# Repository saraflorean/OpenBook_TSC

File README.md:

# OpenBook_TSC

## Florean Sara-Denisa - 333CD

# Diagrama Block

---

# Descrierea modulelor hardware

## Microcontroler – ESP32-C6-WROOM-1-N8

ESP32-C6 este unitatea centrală de procesare responsabilă pentru gestionarea tuturor operațiunilor sistemului, comunicarea cu senzorii și modulele, precum și managementul energiei.

- **Arhitectură:** RISC-V pe 32 de biți  
- **Frecvență ceas:** 160 MHz  
- **Conectivitate wireless:** Wi-Fi 6 la 2.4 GHz, Bluetooth 5.0  

## Management Energetic & Baterie

- **Tip baterie:** Li-Po (Litiu-Polimer)  
- **Capacitate:** 3.7V, 1800mAh  
- **Circuit de încărcare:** MCP73831T  
- **Tensiune de intrare:** 5V prin USB-C  
- **Protecții:** Protecție la supraîncărcare și descărcare profundă  
- **Regulator de tensiune:** Regulator LDO care asigură o alimentare stabilă de 3.3V pentru toate componentele
  
## Afișaj – Ecran E-Paper (E-Ink)

- **Dimensiune:** 7.5 inci  
- **Rezoluție:** 800x480 pixeli  
- **Interfață de comunicare:** SPI  

## Modul Card SD

- **Tip:** MicroSD (Suportă FAT32)  
- **Interfață:** SPI  

## Memorie NOR Flash Externă

- **Capacitate:** 64MB  
- **Interfață:** SPI  

## Senzor de Mediu – BME688

- **Funcții:** Măsoară temperatura, umiditatea, presiunea aerului și nivelurile de gaz  
- **Interfață de comunicare:** I2C  

## Ceas în Timp Real (RTC) – DS3231SN

- **Funcționalitate:** Păstrează ora și data chiar și atunci când sistemul este oprit  
- **Interfață de comunicare:** I2C  

## Conector USB-C & Protecție ESD

- **Funcționalitate:** Asigură alimentarea și transferul de date  
- **Protecție:** Protecție ESD integrată și diodă Schottky pentru protecție la polaritate inversă  

## Butoane & Interacțiune cu Utilizatorul

- **Butoane tactile (push):** Utilizate pentru control manual  

## Interfețe de Comunicație

- **GPIO:** Folosit pentru controlul butoanelor și operațiuni generale I/O  
- **SPI:** Utilizat pentru cardul SD, memoria flash externă și ecranul e-paper  
- **I2C:** Utilizat pentru senzorul de mediu BME688 și modulul RTC DS3231SN  
- **UART:** Utilizat pentru depanare și comunicație serială  
- **Wi-Fi & Bluetooth:** Asigurate de ESP32-C6 pentru conectivitate wireless  

---

## Lista Componentelor folosite

| Componentă | Link | Fișă Tehnică |
|-----------|--------------|-----------|
| MAX17048G+T10 | [Model](https://www.snapeda.com/parts/MAX17048G+T10/Analog+Devices/view-part/?ref=eda) | [Datasheet](https://www.alldatasheet.com/view.jsp?Searchword=Max17048&gad_source=1&gbraid=0AAAAADcdDU8aYfZtfJfdZ9I5j6RwZ_cbA&gclid=Cj0KCQjwqcO_BhDaARIsACz62vNa9xrVfzjCjADRwXD0RBbo4Nret3ywwteDGLJKZui8ZL8KdVlTE7caAvQxEALw_wcB) |
| MCP73831T-5ACI/OT | [Model](https://www.mouser.co.uk/ProductDetail/Microchip-Technology/MCP73831T-5ACI-OT?qs=hH%252BOa0VZEiAcgAcEkuamXg%3D%3D) | [Datasheet](//efaidnbmnnnibpcajpcglclefindmkaj/https://ww1.microchip.com/downloads/en/DeviceDoc/MCP73831-Family-Data-Sheet-DS20001984H.pdf) |
| USB4110-GF-A  | [Model](https://componentsearchengine.com/part-view/USB4110-GF-A/GCT%20(GLOBAL%20CONNECTOR%20TECHNOLOGY)) | [Datasheet](//efaidnbmnnnibpcajpcglclefindmkaj/https://gct.co/files/drawings/usb4110.pdf) |
| Adafruit | [Model](https://eu.mouser.com/ProductDetail/Adafruit/4208?qs=PzGy0jfpSMtbScLbr0L5dw%3D%3D) | [Datasheet](https://www.arrow.com/en/manufacturers/adafruit-industries/datasheets) |
| CAPACITOR | [Model](https://componentsearchengine.com/part-view/R0402%201%25%20100%20K%20(RC0402FR-07100KL)/YAGEO) | [Datasheet](//efaidnbmnnnibpcajpcglclefindmkaj/https://www.resistor.com/assets/pdf/0402tstd.pdf) |
| CPH3225A | [Model](https://www.snapeda.com/parts/CPH3225A/Seiko+Instruments/view-part/?ref=eda) | [Datasheet](https://octopart.com/datasheet/cph3225a-seiko-25340571) |
| EVQPUJ02K | [Model](https://industry.panasonic.com/global/en/products/control/switch/light-touch/number/evqpuj02k) | [Datasheet](https://www.lcsc.com/datasheet/lcsc_datasheet_2201121800_PANASONIC-EVQPUJ02K_C2936858.pdf) |
| KP-1608SURCK | [Model](https://www.snapeda.com/parts/KP-1608SURCK/Kingbright/view-part/?ref=search&t=LED%200603) | [Datasheet](//efaidnbmnnnibpcajpcglclefindmkaj/https://media.elv.com/file/107153_led_surck1608_data.pdf) |
| USBLC6-2SC6Y | [Model](https://www.snapeda.com/parts/USBLC6-2SC6Y/STMicroelectronics/view-part/?ref=eda) | [Datasheet](https://www.digikey.com/en/htmldatasheets/production/1375342/0/0/1/usblc6-2sc6y) |
| SD0805S020S1R0 | [Model](https://ro.mouser.com/ProductDetail/KYOCERA-AVX/SD0805S020S1R0?qs=jCA%252BPfw4LHbpkAoSnwrdjw%3D%3D) | [Datasheet](https://www.alldatasheet.com/view.jsp?Searchword=SD0805S&sField=2) |
| PGB1010603MR | [Model](https://www.snapeda.com/parts/PGB1010603MR/Littelfuse/view-part/?ref=eda) | [Datasheet](https://www.alldatasheet.com/view.jsp?Searchword=Pgb1010603mr&gad_source=1&gbraid=0AAAAADcdDU8aYfZtfJfdZ9I5j6RwZ_cbA&gclid=Cj0KCQjwqcO_BhDaARIsACz62vOPBOBe0eOh5gDUFkkKl4JBcbmoFZYtJ8BOnbaWqr_BuUCcVWvbutAaAmGkEALw_wcB) |
| BD5229G-TR  | [Model](https://componentsearchengine.com/part-view/BD5229G-TR/ROHM%20Semiconductor) | [Datasheet](https://www.lcsc.com/datasheet/lcsc_datasheet_2201131330_ROHM-Semicon-BD5229G-TR_C962636.pdf) |
| BME680 | [Model](https://www.snapeda.com/parts/BME680/Bosch/view-part/?welcome=home) | [Datasheet](//efaidnbmnnnibpcajpcglclefindmkaj/https://www.bosch-sensortec.com/media/boschsensortec/downloads/datasheets/bst-bme680-ds001.pdf) |
| XC6220A331MR-G | [Model](https://componentsearchengine.com/part-view/XC6220A331MR-G/Torex) | [Datasheet](https://www.alldatasheet.com/view.jsp?Searchword=Xc6220&gad_source=1&gbraid=0AAAAADcdDU8aYfZtfJfdZ9I5j6RwZ_cbA&gclid=Cj0KCQjwqcO_BhDaARIsACz62vPS06NB6tLgniZzfaVpKNu1m811BNk6AEPfg4DbP6f5S8QWA_pW_UQaAv-0EALw_wcB) |
| SMD Solder | [Model](https://grabcad.com/library/solder-jumpers-1) | [Datasheet]() |
| BUTTON | [Model](https://industry.panasonic.com/global/en/products/control/switch/light-touch/number/evqpuj02k) | [Datasheet](https://www.lcsc.com/datasheet/lcsc_datasheet_2201121800_PANASONIC-EVQPUJ02K_C2936858.pdf) |
| Bobina | [Model](https://store.comet.srl.ro/Catalogue/Product/43497/) | [Datasheet](https://www.scribd.com/document/814581278/Datasheet-Bobina) |
| PFMF | [Model](https://www.mouser.co.uk/ProductDetail/EPCOS-TDK/B72520T0350K062?qs=dEfas%2FXlABIszF52uu7vrg%3D%3D) | [Datasheet](https://ro.mouser.com/c/ds/circuit-protection/thermistors/resettable-fuses-pptc/?m=Schurter&series=PFMF) |
| DMG2305UX-7 | [Model](https://componentsearchengine.com/part-view/DMG2305UX-7/Diodes%20Incorporated) | [Datasheet](//efaidnbmnnnibpcajpcglclefindmkaj/https://www.mouser.com/datasheet/2/115/DMG2305UX-266242.pdf?srsltid=AfmBOop22k34YTJJra1xubiU6LPiN4M4JlcWbRoSNdxSGFak8uWgXPpK) |
| Si1308EDL-T1-GE3 | [Model](https://componentsearchengine.com/part-view/SI1308EDL-T1-GE3/Vishay) | [Datasheet](https://www.alldatasheet.com/view.jsp?Searchword=Si1308edl&gad_source=1&gbraid=0AAAAADcdDU-px713ONYSnQ2O-gcwqYcFq&gclid=Cj0KCQjwqcO_BhDaARIsACz62vN_Nz3MJOc6J_03gnVBm7aSqC8v9wyP0VD-iRKP-gFrYgdhLi99I14aAlVJEALw_wcB) |
| R0402 | [Model](https://componentsearchengine.com/part-view/R0402%201%25%20100%20K%20(RC0402FR-07100KL)/YAGEO) | [Datasheet](//efaidnbmnnnibpcajpcglclefindmkaj/https://www.resistor.com/assets/pdf/0402tstd.pdf) |
| W25Q512JVEIQ | [Model](https://www.snapeda.com/parts/ESP32-C6-WROOM-1-N8/Espressif+Systems/view-part/?ref=eda) | [Datasheet](//efaidnbmnnnibpcajpcglclefindmkaj/https://www.mouser.com/datasheet/2/949/W25Q512JV_SPI_RevB_06252019_KMS-2487502.pdf?srsltid=AfmBOoquExqDVgxEELF9CzuOGxHos0CD1nQDROHD6Eebdm2foNzqozqU) |
| ESP32-C6-WROOM-1-N8 | [Model](https://www.snapeda.com/parts/ESP32-C6-WROOM-1-N8/Espressif+Systems/view-part/?ref=eda) | [Datasheet](//efaidnbmnnnibpcajpcglclefindmkaj/https://www.mouser.com/catalog/specsheets/Espressif_ESP32_C6_WROOM_1%20_Datasheet_V0.1_PRELIMINARY_en.pdf?srsltid=AfmBOooHQKNitqODRaaPjoZInfWKTacDER1t5uRK6sKqT13TrzvVo_B7) |
| DS3231SN# | [Model](https://www.snapeda.com/parts/DS3231SN%23/Analog+Devices/view-part/?ref=eda) | [Datasheet](https://www.alldatasheet.com/view.jsp?Searchword=Ds3231sn%20datasheet&gad_source=1&gbraid=0AAAAADcdDU-Gy9URfMxGmqiPg7ci5L3wR&gclid=Cj0KCQjwqcO_BhDaARIsACz62vMkK3ETSnW2w7mo0Fa-wgWJGn89AxWCyIND6k5X8MmoPl6hv6VWwT8aAiS-EALw_wcB) |

---

## Mapare Pini – ESP32-C6

| Denumire       | Pin GPIO      | Utilizare                                |
|----------------|---------------|------------------------------------------|
| Buton Reset    | EN            | Resetare ESP32-C6                        |
| INT_RTC        | IO0           | Semnal de întrerupere de la RTC (DS3231)|
| 32KHZ          | IO1           | Semnal de ceas 32 kHz                    |
| MISO (SPI)     | IO2           | Recepție date SPI                        |
| EPD BUSY       | IO3           | Indicator stare E-Paper                  |
| SS_SD          | IO4           | Chip Select pentru card SD (SPI)        |
| EPD DC         | IO5           | Data/Command pentru E-Paper             |
| SCK (SPI)      | IO6           | Clock pentru SPI                         |
| MOSI (SPI)     | IO7           | Transmitere date SPI                     |
| Buton Boot     | IO9           | Intrare în bootloader                    |
| 3V3            | 3V3           | Alimentare 3.3V                          |
| EPD_CS         | IO10          | Selectare SPI pentru E-Paper            |
| FLASH_CS       | IO11          | Selectare SPI pentru NOR Flash          |
| USB_D-         | IO12          | Linie diferențială USB (minus)          |
| USB_D+         | IO13          | Linie diferențială USB (plus)           |
| Buton Change   | IO15          | Schimbare mod operare                    |
| TX (UART)      | TXD0/GPIO16   | Transmitere date UART                   |
| RX (UART)      | RXD0/GPIO17   | Recepție date UART                      |
| RTC_RST        | IO18          | Reset extern/semnal RTC                 |
| I2C_PW         | IO19          | Linie de alimentare / enable pentru I2C |
| EPD_3V3_C      | IO20          | Linie de alimentare 3.3V pentru E-Paper |
| SDA (I2C)      | IO21          | Linie de date I2C                       |
| SCL (I2C)      | IO22          | Linie de ceas I2C                       |
| EPD RST        | IO23          | Resetare E-Paper                        |

---

## Informații adiționale

**Erori SMD-Hole Board Outline Clearance la Mufa USB:**  
  - Am identificat două erori de tip **SMD-Hole Board Outline Clearance** asociate mufei USB. Conform informațiilor tehnice primite, aceste erori au fost **acceptate**.

**Redimensionarea și amplasarea componentelor:**
  - Dimensiunile unor componente au fost **ajustate** pentru a rezolva incompatibilitățile detectate de verificatorul de design.
  - Condensatori de decuplare de 100nF au fost **amplasați aproape de pinii de alimentare** ai circuitelor integrate (IC), în conformitate cu practicile standard de proiectare pentru reducerea zgomotului electric.
  - Componentele au fost amplasate respectând pe cât de mult posibil **specifcațiile proiectului** asigurând compatibilitatea dintre carcasa oferită și dimensiunile PCB-ului.
  - **TP-urile** au fost amplasate diferit față de specificațiile oferite, pentru a facilita o rutare eficientă. Poziția lor fiind determinată de apropierea de piesele conectate.

 **Rutare și planuri de masă**
 - **Traseele de alimentare** au fost rutate **doar pe stratul superior**, ceea ce a necesitat utilizarea a aproximativ 100 de vias-uri pentru a permite rutarea semnalelor pe stratul inferior.
 - **Planul de masă** (GND) a fost adăugat după finalizarea rutării, aplicat atât pe stratul superior, cât și pe cel inferior, pentru a asigura o împământare cu impedanță redusă și pentru a diminua interferențele electromagnetice (EMI).
 - Am realizat **via stitching** în regiunile unde planurile de masă de pe stratul superior și inferior se suprapuneau, pentru a asigura o conexiune electrică solidă între acestea.

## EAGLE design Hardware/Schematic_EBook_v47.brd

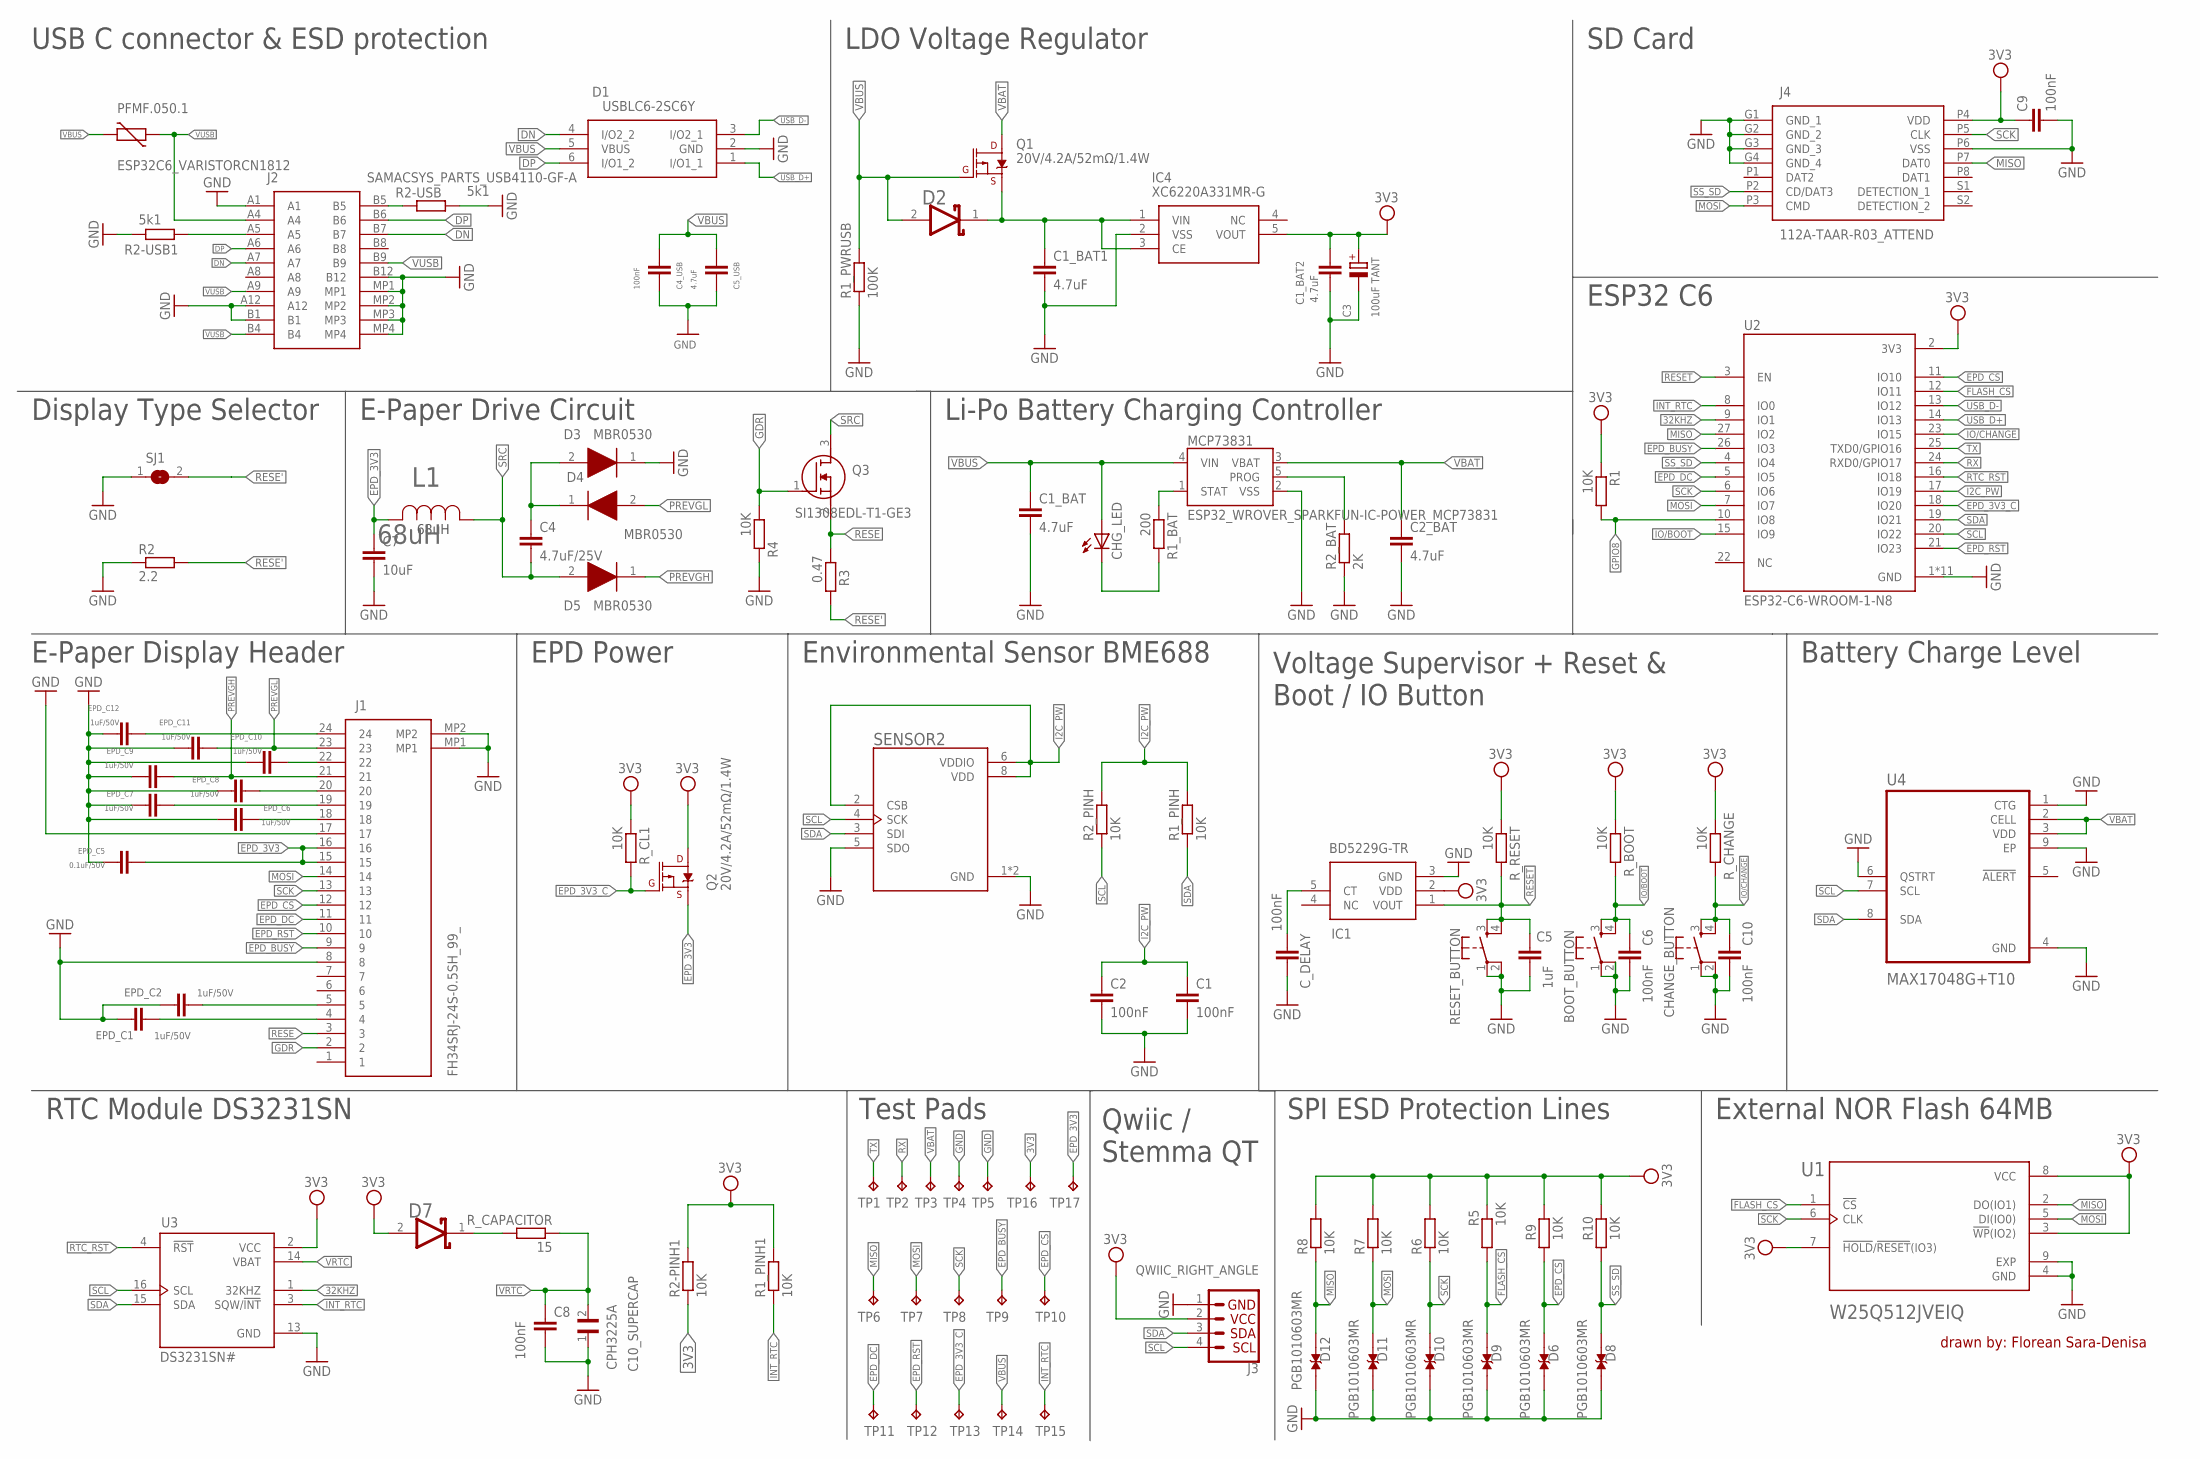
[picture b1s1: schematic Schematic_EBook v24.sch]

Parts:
BOOT_BUTTON: BUTTON_CUSYOMV1; MYBUTTON
C1, C2, C4_USB, C6, C8, C9, C10: 100nF; EAGLE-LTSPICE_C0402
C1_BAT, C1_BAT1, C1_BAT2, C2_BAT, C5_USB: 4.7uF; EAGLE-LTSPICE_C0402
C3: 100uF TANT; RCL_CT3528
C4: 4.7uF/25V; EAGLE-LTSPICE_C0402
C5: 1uF; EAGLE-LTSPICE_C0402
C7: 10uF; EAGLE-LTSPICE_C0402
C10_SUPERCAP: CPH3225A; CAPCP3225X100N
CHANGE_BUTTON: BUTTON_CUSYOMV1; MYBUTTON
CHG_LED: &; ADAFRUIT_CHIP-LED0603
C_DELAY: 100nF; EAGLE-LTSPICE_C0402
D1: USBLC6-2SC6Y; SOT95P280X145-6N
D2, D7: ESP32_WROVER_AVX---SD0805S020S1R0_AVX_SD0805S020S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; ESP32_WROVER_AVX---SD0805S020S1R0_AVX_SD0805S020S1R0_0
D3, D4, D5: MBR0530; SOD3716X135N
D6, D8, D9, D10, D11, D12: PGB1010603MR; DIOC1608X36N
EPD_C1, EPD_C2, EPD_C6, EPD_C7, EPD_C8, EPD_C9, EPD_C10, EPD_C11, EPD_C12: 1uF/50V; EAGLE-LTSPICE_C0402
EPD_C5: 0.1uF/50V; EAGLE-LTSPICE_C0402
IC1: BD5229G-TR; SOT95P280X125-5N
IC4: XC6220A331MR-G; SOT95P280X120-5N
J1: FH34SRJ-24S-0.5SH_99_; FH34SRJ24S05SH99
J2: SAMACSYS_PARTS_USB4110-GF-A; SAMACSYS_PARTS_USB4110GFA
J3: QWIIC_RIGHT_ANGLE; JST04_1MM_RA
J4: 112A-TAAR-R03_ATTEND; 112ATAARR03ATTEND
L1: 68uH; IND_4828-WE-TPC_WRE
MCP73831: ESP32_WROVER_SPARKFUN-IC-POWER_MCP73831; ESP32_WROVER_SPARKFUN-IC-POWER_SOT23-5
PFMF.050.1: ESP32C6_VARISTORCN1812; ESP32C6_VARISTOR_CT/CN1812
Q1, Q2: 20V/4.2A/52mΩ/1.4W; ESP32_WROVER_SPARKFUN-DISCRETESEMI_SOT23-3
Q3: SI1308EDL-T1-GE3; SOT65P210X110-3N
R1, R1_PINH, R1_PINH1, R2-PINH1, R2_PINH, R4, R5, R6, R7, R8, R9, R10: 10K; ESP32_WROVER_EAGLE-LTSPICE_R0402
R1_BAT: 200; ESP32_WROVER_EAGLE-LTSPICE_R0402
R1_PWRUSB: 100K; ESP32_WROVER_EAGLE-LTSPICE_R0402
R2: 2.2; ESP32_WROVER_EAGLE-LTSPICE_R0402
R2-USB, R2-USB1: 5k1; ESP32_WROVER_EAGLE-LTSPICE_R0402
R2_BAT: 2K; ESP32_WROVER_EAGLE-LTSPICE_R0402
R3: 0.47; ESP32_WROVER_EAGLE-LTSPICE_R0402
RESET_BUTTON: BUTTON_CUSYOMV1; MYBUTTON
R_BOOT: 10K; ESP32_WROVER_EAGLE-LTSPICE_R0402
R_CAPACITOR: 15; ESP32_WROVER_EAGLE-LTSPICE_R0402
R_CHANGE: 10K; ESP32_WROVER_EAGLE-LTSPICE_R0402
R_CL1: 10K; ESP32_WROVER_EAGLE-LTSPICE_R0402
R_RESET: 10K; ESP32_WROVER_EAGLE-LTSPICE_R0402
SENSOR2: ESP32_WROVER_BME680_BME680; ESP32_WROVER_BME680_PSON80P300X300X100-8N
SJ1: &; SJ
TP1, TP2, TP3, TP4, TP5, TP6, TP7, TP8, TP9, TP10, TP11, TP12, TP13, TP14, TP15, TP16, TP17: TPTP20R; TP20R
U1: W25Q512JVEIQ; SON127P600X800X80-9N
U2: ESP32-C6-WROOM-1-N8; XCVR_ESP32-C6-WROOM-1-N8
U3: DS3231SN#; SOIC127P1032X265-16N
U4: MAX17048G+T10; SON50P200X200X80-9N

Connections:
3V3: C1_BAT2.1, C3.+, C9.1, D7.2 (ANODE), IC1.2 (VDD), IC4.5 (VOUT), J3.2, J4.P4 (VDD), Q2.3 (D), R1.1, R1_PINH1.2, R2-PINH1.1, R2-PINH1.2, R5.2, R6.2, R7.2, R8.2, R9.2, R10.2, R_BOOT.1, R_CHANGE.1, R_CL1.1, R_RESET.1, TP16.TP, U1.3 (!WP!(IO2)), U1.7 (!HOLD!/!RESET!(IO3)), U1.8 (VCC), U2.2 (3V3), U3.2 (VCC)
32KHZ: U2.9 (IO1), U3.1 (32KHZ)
DN: D1.4 (I/O2_2), J2.A7, J2.B7
DP: D1.6 (I/O1_2), J2.A6, J2.B6
EPD_3V3: C7.1, EPD_C5.1, J1.15, J1.16, L1.2, Q2.2 (S), TP17.TP
EPD_3V3_C: Q2.1 (G), R_CL1.2, TP13.TP, U2.18 (IO20)
EPD_BUSY: J1.9, TP9.TP, U2.26 (IO3)
EPD_CS: D6.2, J1.12, R9.1, TP10.TP, U2.11 (IO10)
EPD_DC: J1.11, TP11.TP, U2.5 (IO5)
EPD_RST: J1.10, TP12.TP, U2.21 (IO23)
FLASH_CS: D9.2, R5.1, U1.1 (!CS), U2.12 (IO11)
GDR: J1.2, Q3.1 (G), R4.1
GND: BOOT_BUTTON.1, BOOT_BUTTON.2, C1.2, C1_BAT.2, C1_BAT1.2, C1_BAT2.2, C2.2, C2_BAT.2, C3.-, C4_USB.2, C5.2, C5_USB.2, C6.2, C7.2, C8.2, C9.2, C10.2, C10_SUPERCAP.1, CHANGE_BUTTON.1, CHANGE_BUTTON.2, C_DELAY.2, D1.2 (GND), D3.1 (K), D6.1, D8.1, D9.1, D10.1, D11.1, D12.1, EPD_C1.2, EPD_C2.2, EPD_C5.2, EPD_C6.2, EPD_C7.2, EPD_C8.2, EPD_C9.2, EPD_C10.2, EPD_C11.2, EPD_C12.2, IC1.3 (GND), IC4.2 (VSS), J1.8, J1.17, J1.MP1, J1.MP2, J2.A1, J2.A12, J2.B1, J2.B12, J2.MP1, J2.MP2, J2.MP3, J2.MP4, J3.1, J4.G1 (GND_1), J4.G2 (GND_2), J4.G3 (GND_3), J4.G4 (GND_4), J4.P6 (VSS), MCP73831.2 (VSS), R1_PWRUSB.1, R2.1, R2-USB.2, R2-USB1.1, R2_BAT.1, R4.2, RESET_BUTTON.1, RESET_BUTTON.2, SENSOR2.1 (GND), SENSOR2.5 (SDO), SENSOR2.7 (GND), SJ1.1, TP4.TP, TP5.TP, U1.4 (GND), U1.9 (EXP), U2.1 (GND), U2.28 (GND), U2.29_1 (GND), U2.29_2 (GND), U2.29_3 (GND), U2.29_4 (GND), U2.29_5 (GND), U2.29_6 (GND), U2.29_7 (GND), U2.29_8 (GND), U2.29_9 (GND), U3.13 (GND), U4.1 (CTG), U4.4 (GND), U4.6 (QSTRT), U4.9 (EP)
GPIO8: R1.2, U2.10 (IO8)
I2C_PW: C1.1, C2.1, R1_PINH.2, R2_PINH.2, SENSOR2.2 (CSB), SENSOR2.6 (VDDIO), SENSOR2.8 (VDD), U2.17 (IO19)
INT_RTC: R1_PINH1.1, TP15.TP, U2.8 (IO0), U3.3 (SQW/!INT)
IO/BOOT: BOOT_BUTTON.3, BOOT_BUTTON.4, C6.1, R_BOOT.2, U2.15 (IO9)
IO/CHANGE: C10.1, CHANGE_BUTTON.3, CHANGE_BUTTON.4, R_CHANGE.2, U2.23 (IO15)
MISO: D12.2, J4.P7 (DAT0), R8.1, TP6.TP, U1.2 (DO(IO1)), U2.27 (IO2)
MOSI: D11.2, J1.14, J4.P3 (CMD), R7.1, TP7.TP, U1.5 (DI(IO0)), U2.7 (IO7)
unnamed: J2.A5, R2-USB1.2
unnamed: J2.B5, R2-USB.1
unnamed: C1_BAT1.1, D2.1 (CATHODE), IC4.1 (VIN), IC4.3 (CE), Q1.2 (S)
unnamed: MCP73831.1 (STAT), R1_BAT.1
unnamed: C4.1, D3.2 (A), D4.1 (K)
unnamed: CHG_LED.C, R1_BAT.2
unnamed: MCP73831.5 (PROG), R2_BAT.2
unnamed: EPD_C2.1, J1.5
unnamed: EPD_C1.1, J1.4
unnamed: C_DELAY.1, IC1.5 (CT)
unnamed: D7.1 (CATHODE), R_CAPACITOR.2
unnamed: EPD_C12.1, J1.24
unnamed: EPD_C10.1, J1.22
unnamed: EPD_C8.1, J1.20
unnamed: EPD_C6.1, J1.18
unnamed: EPD_C7.1, J1.19
PREVGH: D5.1 (K), EPD_C9.1, J1.21
PREVGL: D4.2 (A), EPD_C11.1, J1.23
RESE: J1.3, Q3.2 (S), R3.1
RESE': R2.2, R3.2, SJ1.2
RESET: C5.1, IC1.1 (VOUT), RESET_BUTTON.3, RESET_BUTTON.4, R_RESET.2, U2.3 (EN)
RTC_RST: U2.16 (IO18), U3.4 (!RST)
RX: TP2.TP, U2.24 (RXD0/GPIO17)
SCK: D10.2, J1.13, J4.P5 (CLK), R6.1, TP8.TP, U1.6 (CLK), U2.6 (IO6)
SCL: J3.4, R2_PINH.1, SENSOR2.4 (SCK), U2.20 (IO22), U3.16 (SCL), U4.7 (SCL)
SDA: J3.3, R1_PINH.1, SENSOR2.3 (SDI), U2.19 (IO21), U3.15 (SDA), U4.8 (SDA)
SRC: C4.2, D5.2 (A), L1.1, Q3.3 (D)
SS_SD: D8.2, J4.P2 (CD/DAT3), R10.1, U2.4 (IO4)
TX: TP1.TP, U2.25 (TXD0/GPIO16)
USB_D+: D1.1 (I/O1_1), U2.14 (IO13)
USB_D-: D1.3 (I/O2_1), U2.13 (IO12)
VBAT: C2_BAT.1, MCP73831.3 (VBAT), Q1.3 (D), TP3.TP, U4.2 (CELL), U4.3 (VDD)
VBUS: C1_BAT.1, C4_USB.1, C5_USB.1, CHG_LED.A, D1.5 (VBUS), D2.2 (ANODE), MCP73831.4 (VIN), PFMF.050.1.2, Q1.1 (G), R1_PWRUSB.2, TP14.TP
VRTC: C8.1, C10_SUPERCAP.2, R_CAPACITOR.1, U3.14 (VBAT)
VUSB: J2.A4, J2.A9, J2.B4, J2.B9, PFMF.050.1.1

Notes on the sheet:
68uH
USB C connector & ESD protection
LDO Voltage Regulator
SD Card
ESP32 C6
Li-Po Battery Charging Controller
E-Paper Drive Circuit
Display Type Selector
E-Paper Display Header
EPD Power
Environmental Sensor BME688
Voltage Supervisor + Reset & Boot / IO Button
Battery Charge Level
External NOR Flash 64MB
SPI ESD Protection Lines
Qwiic / Stemma QT
Test Pads
RTC Module DS3231SN
drawn by: Florean Sara-Denisa

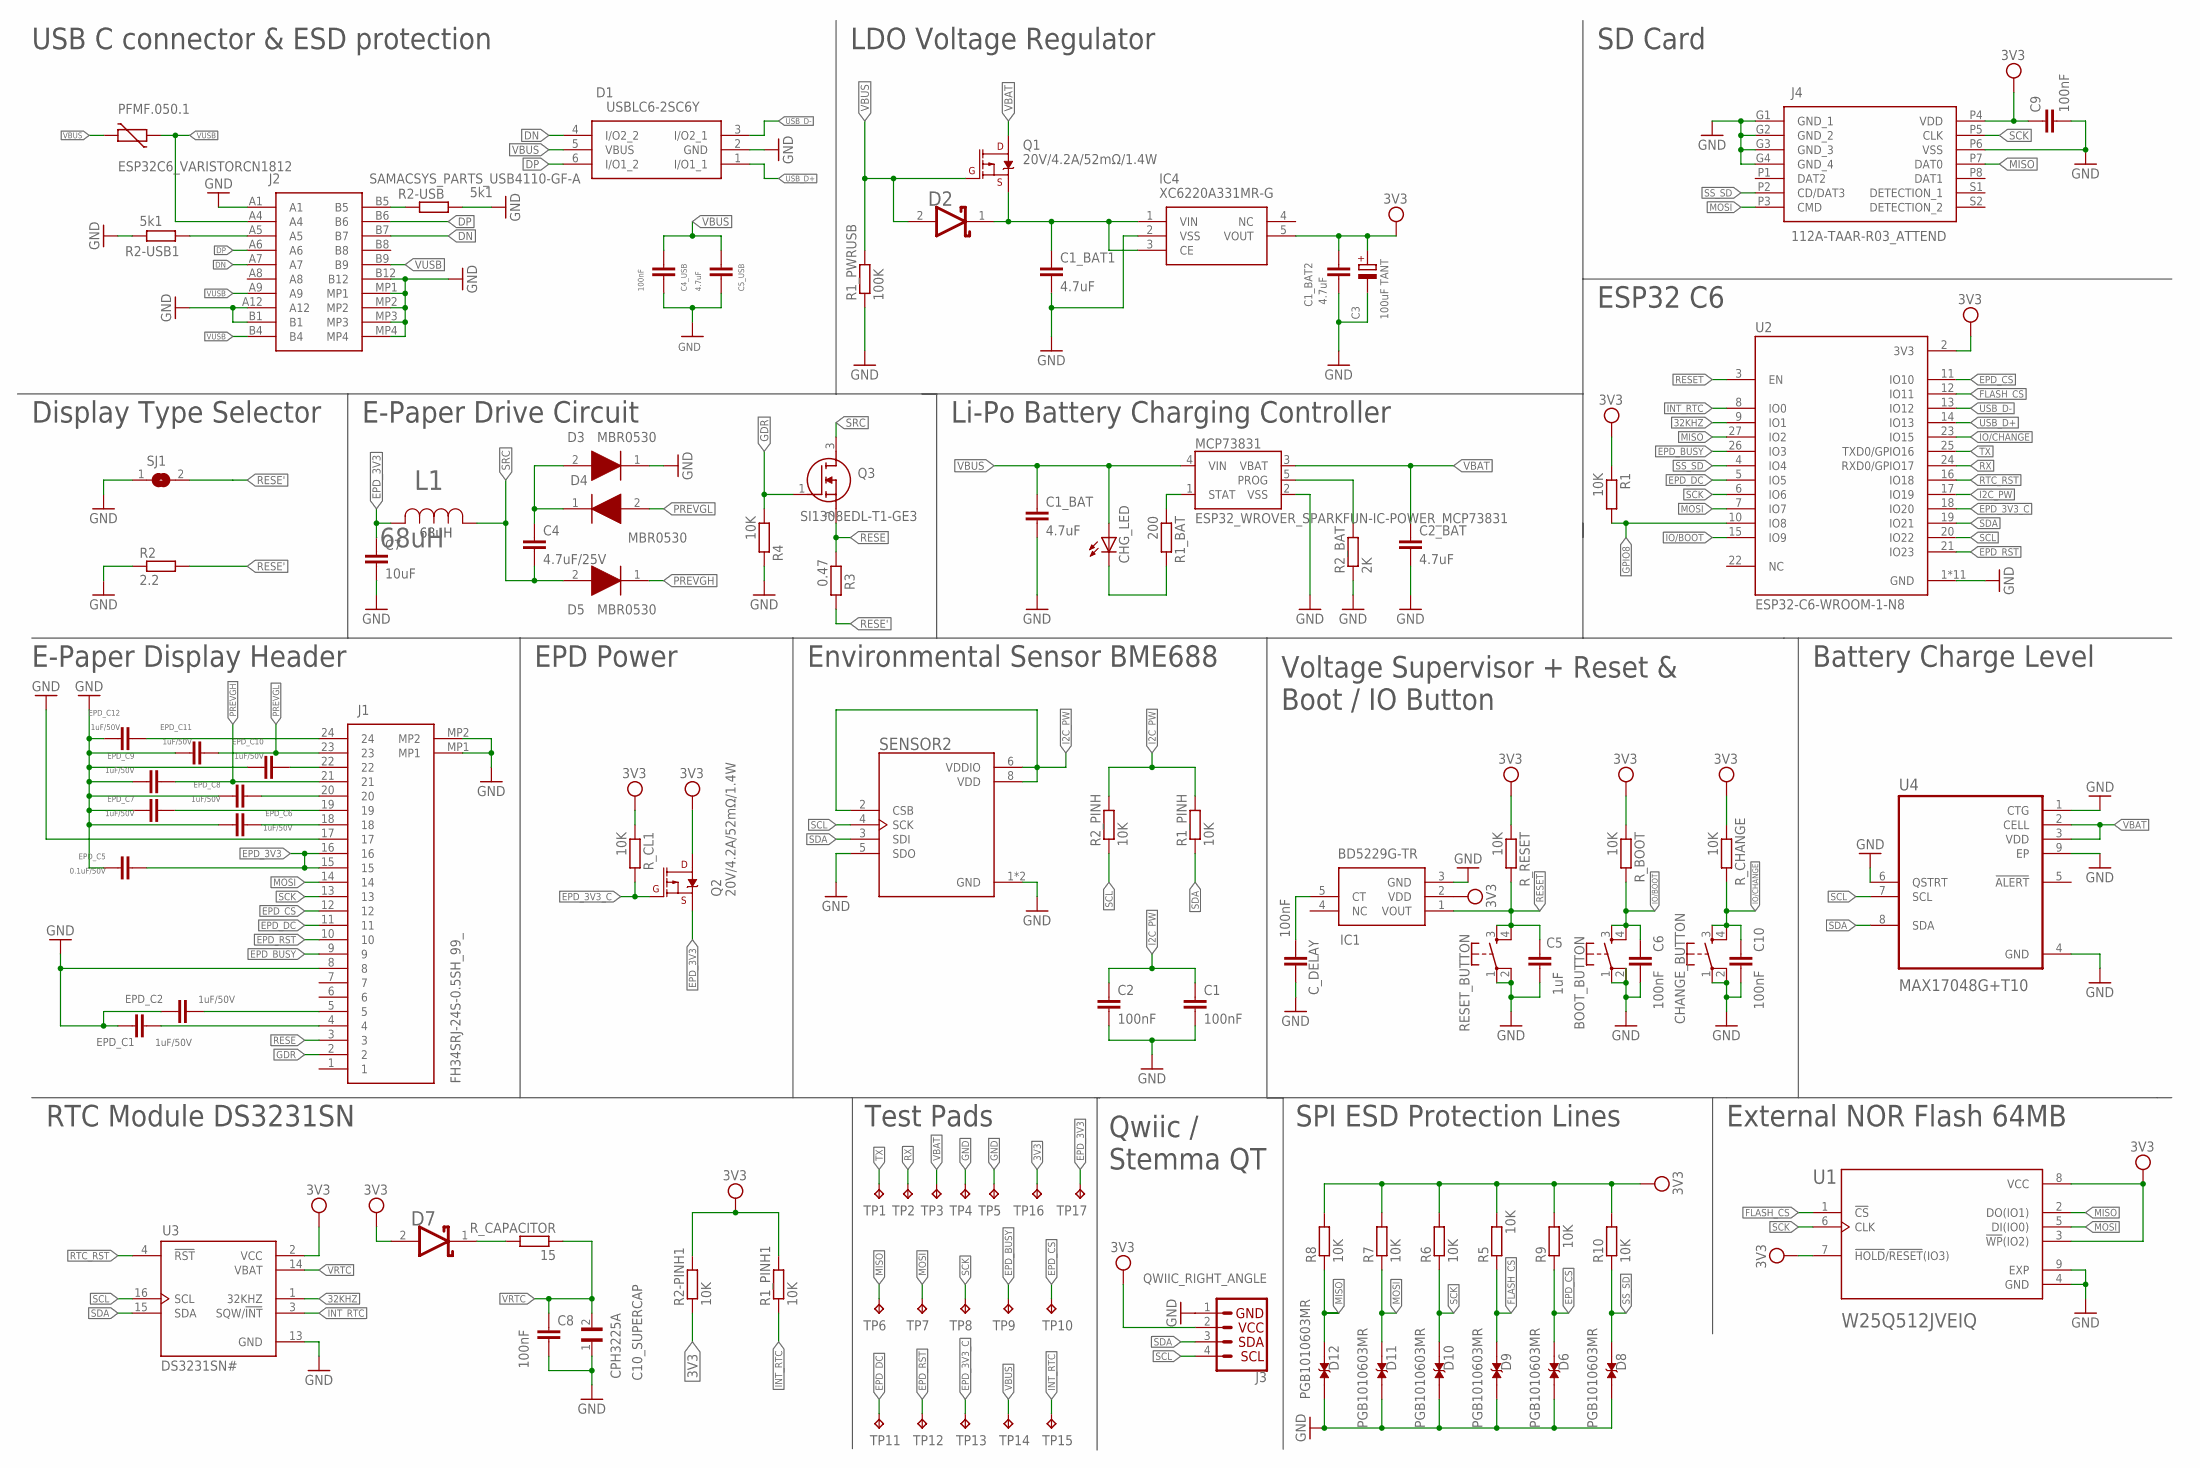
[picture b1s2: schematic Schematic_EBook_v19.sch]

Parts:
BOOT_BUTTON: BUTTON_CUSYOMV1; MYBUTTON
C1, C2, C4_USB, C6, C8, C9, C10: 100nF; EAGLE-LTSPICE_C0402
C1_BAT, C1_BAT1, C1_BAT2, C2_BAT, C5_USB: 4.7uF; EAGLE-LTSPICE_C0402
C3: 100uF TANT; RCL_CT3528
C4: 4.7uF/25V; EAGLE-LTSPICE_C0402
C5: 1uF; EAGLE-LTSPICE_C0402
C7: 10uF; EAGLE-LTSPICE_C0402
C10_SUPERCAP: CPH3225A; CAPCP3225X100N
CHANGE_BUTTON: BUTTON_CUSYOMV1; MYBUTTON
CHG_LED: ADAFRUIT_LEDCHIP-LED0603; ADAFRUIT_CHIP-LED0603
C_DELAY: 100nF; EAGLE-LTSPICE_C0402
D1: USBLC6-2SC6Y; SOT95P280X145-6N
D2, D7: ESP32_WROVER_AVX---SD0805S020S1R0_AVX_SD0805S020S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; ESP32_WROVER_AVX---SD0805S020S1R0_AVX_SD0805S020S1R0_0
D3, D4, D5: MBR0530; SOD3716X135N
D6, D8, D9, D10, D11, D12: PGB1010603MR; DIOC1608X36N
EPD_C1, EPD_C2, EPD_C6, EPD_C7, EPD_C8, EPD_C9, EPD_C10, EPD_C11, EPD_C12: 1uF/50V; EAGLE-LTSPICE_C0402
EPD_C5: 0.1uF/50V; EAGLE-LTSPICE_C0402
IC1: BD5229G-TR; SOT95P280X125-5N
IC4: XC6220A331MR-G; SOT95P280X120-5N
J1: FH34SRJ-24S-0.5SH_99_; FH34SRJ24S05SH99
J2: SAMACSYS_PARTS_USB4110-GF-A; SAMACSYS_PARTS_USB4110GFA
J3: QWIIC_RIGHT_ANGLE; JST04_1MM_RA
J4: 112A-TAAR-R03_ATTEND; 112ATAARR03ATTEND
L1: 68uH; IND_4828-WE-TPC_WRE
MCP73831: ESP32_WROVER_SPARKFUN-IC-POWER_MCP73831; ESP32_WROVER_SPARKFUN-IC-POWER_SOT23-5
PFMF.050.1: ESP32C6_VARISTORCN1812; ESP32C6_VARISTOR_CT/CN1812
Q1, Q2: 20V/4.2A/52mΩ/1.4W; ESP32_WROVER_SPARKFUN-DISCRETESEMI_SOT23-3
Q3: SI1308EDL-T1-GE3; SOT65P210X110-3N
R1, R1_PINH, R1_PINH1, R2-PINH1, R2_PINH, R4, R5, R6, R7, R8, R9, R10: 10K; ESP32_WROVER_EAGLE-LTSPICE_R0402
R1_BAT: 200; ESP32_WROVER_EAGLE-LTSPICE_R0402
R1_PWRUSB: 100K; ESP32_WROVER_EAGLE-LTSPICE_R0402
R2: 2.2; ESP32_WROVER_EAGLE-LTSPICE_R0402
R2-USB, R2-USB1: 5k1; ESP32_WROVER_EAGLE-LTSPICE_R0402
R2_BAT: 2K; ESP32_WROVER_EAGLE-LTSPICE_R0402
R3: 0.47; ESP32_WROVER_EAGLE-LTSPICE_R0402
RESET_BUTTON: BUTTON_CUSYOMV1; MYBUTTON
R_BOOT: 10K; ESP32_WROVER_EAGLE-LTSPICE_R0402
R_CAPACITOR: 15; ESP32_WROVER_EAGLE-LTSPICE_R0402
R_CHANGE: 10K; ESP32_WROVER_EAGLE-LTSPICE_R0402
R_CL1: 10K; ESP32_WROVER_EAGLE-LTSPICE_R0402
R_RESET: 10K; ESP32_WROVER_EAGLE-LTSPICE_R0402
SENSOR2: ESP32_WROVER_BME680_BME680; ESP32_WROVER_BME680_PSON80P300X300X100-8N
SJ1: SJ
TP1, TP2, TP3, TP4, TP5, TP6, TP7, TP8, TP9, TP10, TP11, TP12, TP13, TP14, TP15, TP16, TP17: TPTP20R; TP20R
U1: W25Q512JVEIQ; SON127P600X800X80-9N
U2: ESP32-C6-WROOM-1-N8; XCVR_ESP32-C6-WROOM-1-N8
U3: DS3231SN#; SOIC127P1032X265-16N
U4: MAX17048G+T10; SON50P200X200X80-9N

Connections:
3V3: C1_BAT2.1, C3.+, C9.1, D7.2 (ANODE), IC1.2 (VDD), IC4.5 (VOUT), J3.2, J4.P4 (VDD), Q2.3 (D), R1.1, R1_PINH1.2, R2-PINH1.1, R2-PINH1.2, R5.2, R6.2, R7.2, R8.2, R9.2, R10.2, R_BOOT.1, R_CHANGE.1, R_CL1.1, R_RESET.1, TP16.TP, U1.3 (!WP!(IO2)), U1.7 (!HOLD!/!RESET!(IO3)), U1.8 (VCC), U2.2 (3V3), U3.2 (VCC)
32KHZ: U2.9 (IO1), U3.1 (32KHZ)
DN: D1.4 (I/O2_2), J2.A7, J2.B7
DP: D1.6 (I/O1_2), J2.A6, J2.B6
EPD_3V3: C7.1, EPD_C5.1, J1.15, J1.16, L1.2, Q2.2 (S), TP17.TP
EPD_3V3_C: Q2.1 (G), R_CL1.2, TP13.TP, U2.18 (IO20)
EPD_BUSY: J1.9, TP9.TP, U2.26 (IO3)
EPD_CS: D6.2, J1.12, R9.1, TP10.TP, U2.11 (IO10)
EPD_DC: J1.11, TP11.TP, U2.5 (IO5)
EPD_RST: J1.10, TP12.TP, U2.21 (IO23)
FLASH_CS: D9.2, R5.1, U1.1 (!CS), U2.12 (IO11)
GDR: J1.2, Q3.1 (G), R4.1
GND: BOOT_BUTTON.1, BOOT_BUTTON.2, C1.2, C1_BAT.2, C1_BAT1.2, C1_BAT2.2, C2.2, C2_BAT.2, C3.-, C4_USB.2, C5.2, C5_USB.2, C6.2, C7.2, C8.2, C9.2, C10.2, C10_SUPERCAP.1, CHANGE_BUTTON.1, CHANGE_BUTTON.2, C_DELAY.2, D1.2 (GND), D3.1 (K), D6.1, D8.1, D9.1, D10.1, D11.1, D12.1, EPD_C1.2, EPD_C2.2, EPD_C5.2, EPD_C6.2, EPD_C7.2, EPD_C8.2, EPD_C9.2, EPD_C10.2, EPD_C11.2, EPD_C12.2, IC1.3 (GND), IC4.2 (VSS), J1.8, J1.17, J1.MP1, J1.MP2, J2.A1, J2.A12, J2.B1, J2.B12, J2.MP1, J2.MP2, J2.MP3, J2.MP4, J3.1, J4.G1 (GND_1), J4.G2 (GND_2), J4.G3 (GND_3), J4.G4 (GND_4), J4.P6 (VSS), MCP73831.2 (VSS), R1_PWRUSB.1, R2.1, R2-USB.2, R2-USB1.1, R2_BAT.1, R4.2, RESET_BUTTON.1, RESET_BUTTON.2, SENSOR2.1 (GND), SENSOR2.5 (SDO), SENSOR2.7 (GND), SJ1.1, TP4.TP, TP5.TP, U1.4 (GND), U1.9 (EXP), U2.1 (GND), U2.28 (GND), U2.29_1 (GND), U2.29_2 (GND), U2.29_3 (GND), U2.29_4 (GND), U2.29_5 (GND), U2.29_6 (GND), U2.29_7 (GND), U2.29_8 (GND), U2.29_9 (GND), U3.13 (GND), U4.1 (CTG), U4.4 (GND), U4.6 (QSTRT), U4.9 (EP)
GPIO8: R1.2, U2.10 (IO8)
I2C_PW: C1.1, C2.1, R1_PINH.2, R2_PINH.2, SENSOR2.2 (CSB), SENSOR2.6 (VDDIO), SENSOR2.8 (VDD), U2.17 (IO19)
INT_RTC: R1_PINH1.1, TP15.TP, U2.8 (IO0), U3.3 (SQW/!INT)
IO/BOOT: BOOT_BUTTON.3, BOOT_BUTTON.4, C6.1, R_BOOT.2, U2.15 (IO9)
IO/CHANGE: C10.1, CHANGE_BUTTON.3, CHANGE_BUTTON.4, R_CHANGE.2, U2.23 (IO15)
MISO: D12.2, J4.P7 (DAT0), R8.1, TP6.TP, U1.2 (DO(IO1)), U2.27 (IO2)
MOSI: D11.2, J1.14, J4.P3 (CMD), R7.1, TP7.TP, U1.5 (DI(IO0)), U2.7 (IO7)
unnamed: J2.A5, R2-USB1.2
unnamed: J2.B5, R2-USB.1
unnamed: C1_BAT1.1, D2.1 (CATHODE), IC4.1 (VIN), IC4.3 (CE), Q1.2 (S)
unnamed: MCP73831.1 (STAT), R1_BAT.1
unnamed: C4.1, D3.2 (A), D4.1 (K)
unnamed: CHG_LED.C, R1_BAT.2
unnamed: MCP73831.5 (PROG), R2_BAT.2
unnamed: EPD_C2.1, J1.5
unnamed: EPD_C1.1, J1.4
unnamed: C_DELAY.1, IC1.5 (CT)
unnamed: D7.1 (CATHODE), R_CAPACITOR.2
unnamed: EPD_C12.1, J1.24
unnamed: EPD_C10.1, J1.22
unnamed: EPD_C8.1, J1.20
unnamed: EPD_C6.1, J1.18
unnamed: EPD_C7.1, J1.19
PREVGH: D5.1 (K), EPD_C9.1, J1.21
PREVGL: D4.2 (A), EPD_C11.1, J1.23
RESE: J1.3, Q3.2 (S), R3.1
RESE': R2.2, R3.2, SJ1.2
RESET: C5.1, IC1.1 (VOUT), RESET_BUTTON.3, RESET_BUTTON.4, R_RESET.2, U2.3 (EN)
RTC_RST: U2.16 (IO18), U3.4 (!RST)
RX: TP2.TP, U2.24 (RXD0/GPIO17)
SCK: D10.2, J1.13, J4.P5 (CLK), R6.1, TP8.TP, U1.6 (CLK), U2.6 (IO6)
SCL: J3.4, R2_PINH.1, SENSOR2.4 (SCK), U2.20 (IO22), U3.16 (SCL), U4.7 (SCL)
SDA: J3.3, R1_PINH.1, SENSOR2.3 (SDI), U2.19 (IO21), U3.15 (SDA), U4.8 (SDA)
SRC: C4.2, D5.2 (A), L1.1, Q3.3 (D)
SS_SD: D8.2, J4.P2 (CD/DAT3), R10.1, U2.4 (IO4)
TX: TP1.TP, U2.25 (TXD0/GPIO16)
USB_D+: D1.1 (I/O1_1), U2.14 (IO13)
USB_D-: D1.3 (I/O2_1), U2.13 (IO12)
VBAT: C2_BAT.1, MCP73831.3 (VBAT), Q1.3 (D), TP3.TP, U4.2 (CELL), U4.3 (VDD)
VBUS: C1_BAT.1, C4_USB.1, C5_USB.1, CHG_LED.A, D1.5 (VBUS), D2.2 (ANODE), MCP73831.4 (VIN), PFMF.050.1.2, Q1.1 (G), R1_PWRUSB.2, TP14.TP
VRTC: C8.1, C10_SUPERCAP.2, R_CAPACITOR.1, U3.14 (VBAT)
VUSB: J2.A4, J2.A9, J2.B4, J2.B9, PFMF.050.1.1

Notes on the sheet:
68uH
USB C connector & ESD protection
LDO Voltage Regulator
SD Card
ESP32 C6
Li-Po Battery Charging Controller
E-Paper Drive Circuit
Display Type Selector
E-Paper Display Header
EPD Power
Environmental Sensor BME688
Voltage Supervisor + Reset & Boot / IO Button
Battery Charge Level
External NOR Flash 64MB
SPI ESD Protection Lines
Qwiic / Stemma QT
Test Pads
RTC Module DS3231SN

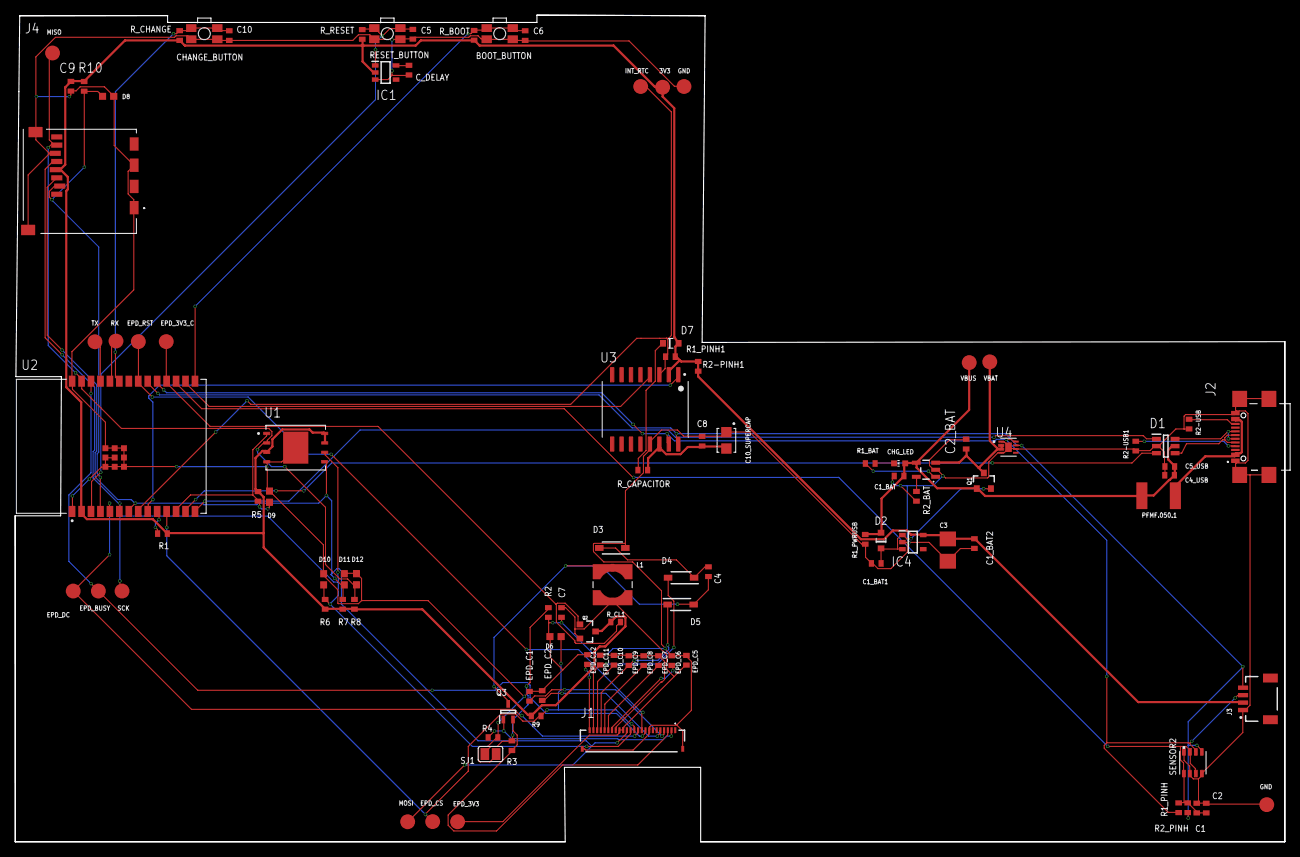
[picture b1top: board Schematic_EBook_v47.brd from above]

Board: 2 copper layers, 170.6 x 111.1 mm, 103 parts (0 on the bottom side), 55 nets.

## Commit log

2025-04-06 Create file
2025-04-06 Add files via upload
    Added gerber and pick and place.
2025-04-06 Add files via upload
    Added 3DFusion360 file
2025-04-06 Create LICENSE
2025-04-06 Add files via upload
    Added photos.

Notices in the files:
parts and their libraries:
DeskAssistant v19 v1: COPYRIGHT: Copyright (C) 2024 Ultra Librarian. All rights reserved.
